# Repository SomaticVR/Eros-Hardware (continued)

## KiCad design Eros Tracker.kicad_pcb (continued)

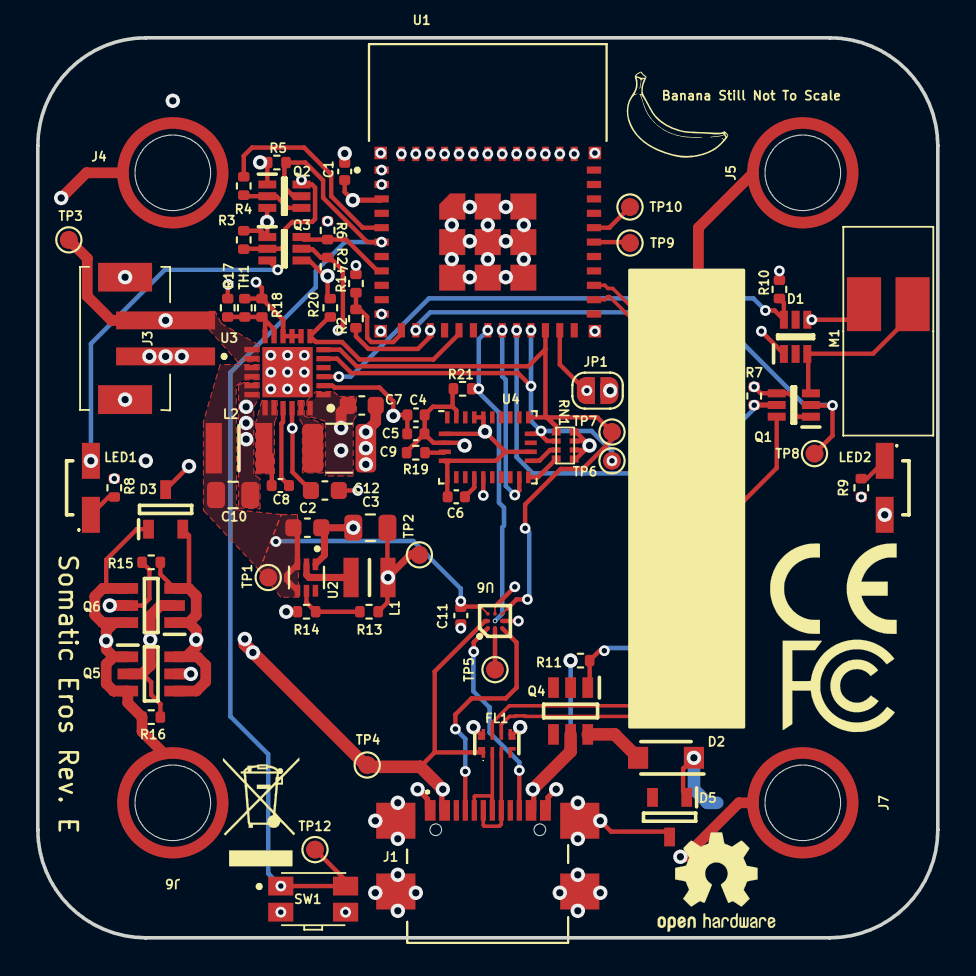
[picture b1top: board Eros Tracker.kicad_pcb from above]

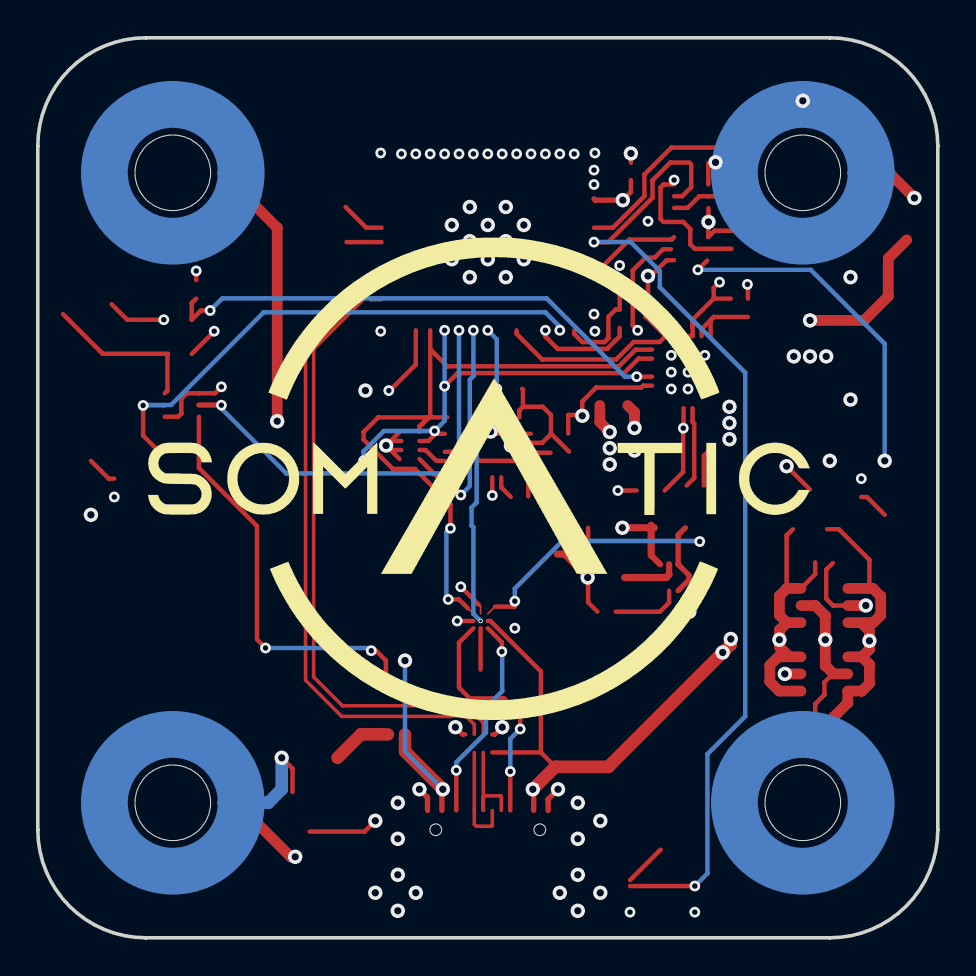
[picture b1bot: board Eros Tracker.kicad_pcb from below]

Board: 4 copper layers, 50.0 x 50.0 mm, 85 parts (5 on the bottom side), 49 nets.

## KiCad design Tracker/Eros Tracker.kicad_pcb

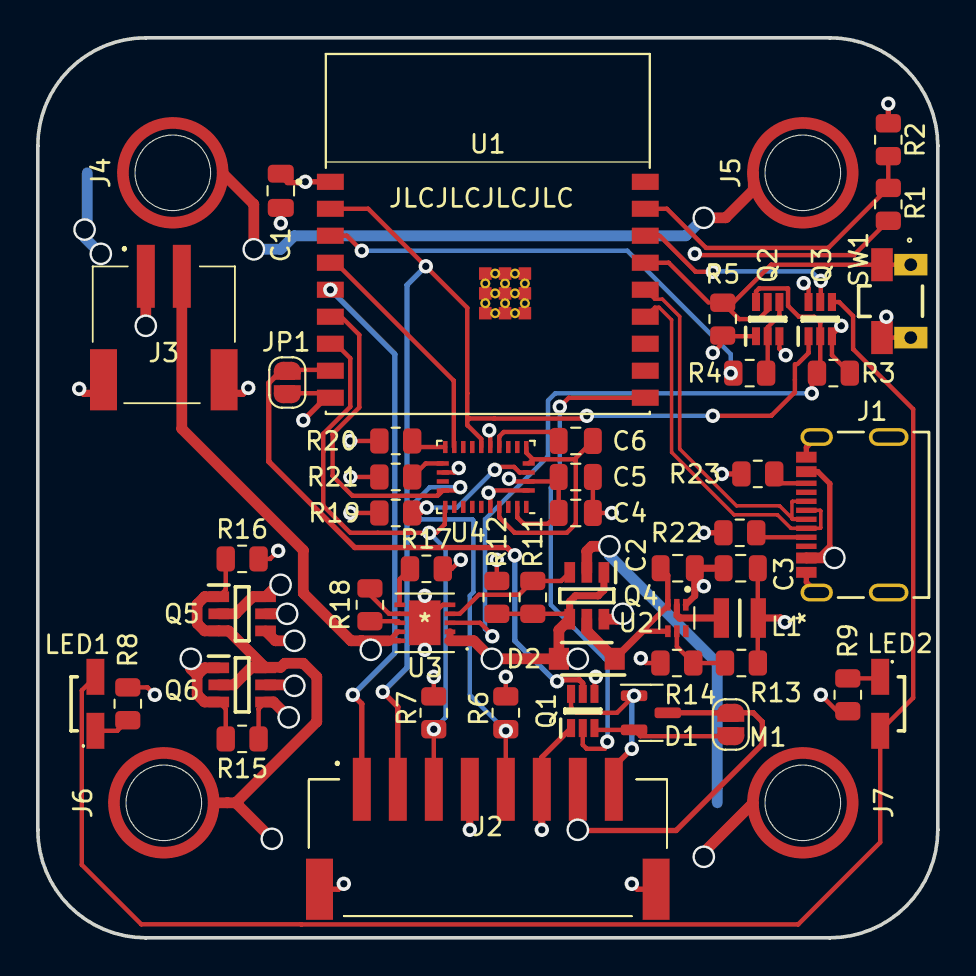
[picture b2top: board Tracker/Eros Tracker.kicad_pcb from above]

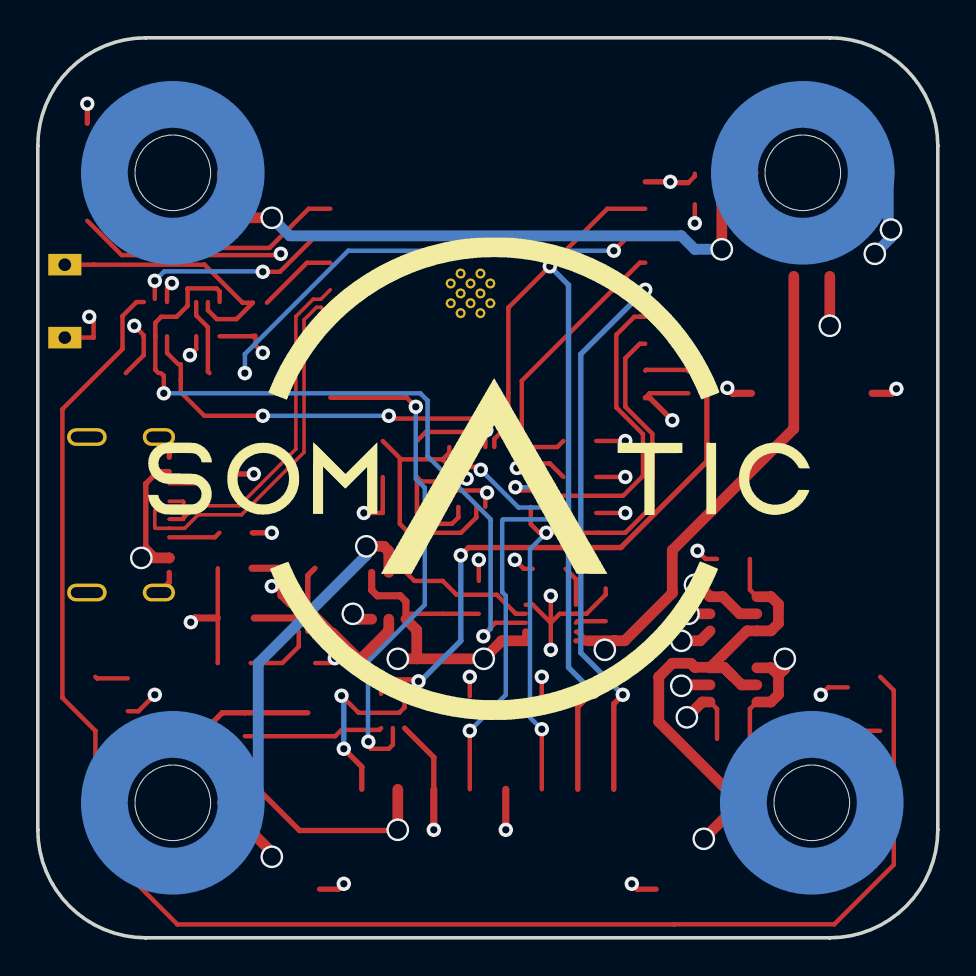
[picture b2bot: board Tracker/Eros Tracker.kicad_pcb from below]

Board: 4 copper layers, 50.0 x 50.0 mm, 57 parts (4 on the bottom side), 40 nets.

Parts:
C1, C4, C5, C6: 0.1uF; C_0805_2012Metric
C2: 4.7uF; C_0805_2012Metric
C3: 22uF; C_0805_2012Metric
D1: BAT54C; SOT-23
D2: SS34FA; SODFL3618X143N
J1: 2171790001; 2171790001_MOL
J2: S8B-PH-SM4-TB(LF)(SN); S8BPHSM4TBLFSN
J3: S2B-PH-SM4-TB(LF)(SN); S2BPHSM4TBLFSN
J4, J5, J6, J7: 24881; 2488x-NPTH
J8, J9, J10, J11: 10mmDisc
JP1: BOOT; SolderJumper-2_P1.3mm_Open_RoundedPad1.0x1.5mm
L1: 1uH; DFE2HCAH1R0MJ0L
LED1, LED2: APDA3020LVBC_D; APDA3020LVBCD
M1: Motor_DC; SolderJumper-2_P1.3mm_Open_RoundedPad1.0x1.5mm
Q1, Q2: NX138BKSX; SOT65P210X110-6N
Q3: DMP31D7LDW-7; SOT65P210X110-6N
Q4: DMP2240UDM-7; SOT95P285X140-6N
Q5, Q6: DMC1028UVT-7; SOT95P285X140-6N
R1, R13: 45k3 1%; R_0805_2012Metric
R2, R5, R11, R12, R14, R15, R16, R18, R19: 10k 1%; R_0805_2012Metric
R3, R4: 100k; R_0805_2012Metric
R6, R7, R20, R21: 2.2k; R_0805_2012Metric
R8, R9: 22R; R_0805_2012Metric
R17: 835R; R_0805_2012Metric
R22, R23: 5k1; R_0805_2012Metric
SW1: EVQ-P7A01P; EVQ-9P701P
U1: ESP32-C3-WROOM-02-N4; ESP32-C3-WROOM-02-N4-MODULE_ESP32-C3-WROOM-02-H4
U2: TPS62A01A; TPS62A0xA-SOT-563
U3: MCP73834-FCI/MF; MCP73834-FCI-MF
U4: BNO086; LGA-28_5.2x3.8mm_P0.5mm

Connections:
+3V3: C1.1, C3.1, C4.1, C5.1, J2.4, L1.2, Q2.3 (D2), Q3.3 (D2), Q3.6 (D1), R3.1, R6.1, R7.1, R13.1, R19.1, R20.1, R21.1, SW1.3 (COM_1), SW1.4 (COM_2), U1.1 (3V3), U4.3 (VDD), U4.10 (CLKSEL0), U4.28 (VDDIO)
+BATT: D1.3, J2.7, J3.2, M1.1 (+), Q4.6 (D1), R1.1, U3.9 (VBAT), U3.10 (VBAT)
/Eros Tracker BNO086 IMU/I2C_SCL: J2.5, R6.2, U1.6 (IO7), U4.19 (H_SCL/SCK/RX)
/Eros Tracker BNO086 IMU/I2C_SDA: J2.3, R7.2, U1.7 (IO8), U4.20 (H_SDA/H_CIPO/TX)
/Eros Tracker BNO086 IMU/INT: U1.4 (IO5), U4.14 (~H_INT)
/Eros Tracker BNO086 IMU/~RESET: J2.2, Q3.1 (S1), U1.2 (EN), U4.11 (~RESET)
/Eros Tracker Connectors/-EXT_MOTOR: D1.1, J2.8, Q1.6 (D1)
/Eros Tracker Connectors/INT: J2.1, U1.5 (IO6)
/Eros Tracker Connectors/POWER_VIN1: J4.1, J5.1, Q5.2 (S2), Q5.6 (D1), Q6.1 (G1), Q6.3 (G2), R15.2
/Eros Tracker Connectors/POWER_VIN2: J6.1, J7.1, Q5.1 (G1), Q5.3 (G2), Q6.2 (S2), Q6.6 (D1), R16.1
/Eros Tracker Connectors/USB_D+: J1.A6 (DP1), J1.B6 (DP2), U1.14 (IO19)
/Eros Tracker Connectors/USB_D-: J1.A7 (DN1), J1.B7 (DN2), U1.13 (IO18)
/Eros Tracker Connectors/VBUS: D2.2 (A), J1.A4/B9 (VBUS), J1.B4/A9 (VBUS), Q4.1 (G1), Q4.4 (D2), Q5.4 (D2), Q6.4 (D2), R11.1, R12.1, R15.1, U3.1 (VDD), U3.2 (VDD)
/Eros Tracker Connectors/VBUS_OUT: J8.1, Q4.2 (S2)
/Eros Tracker Microcontroller/ENABLE_LATCH: R4.1, U1.3 (IO4)
/Eros Tracker Microcontroller/TACT_MOTOR0: JP1.2 (B), Q1.5 (G2), U1.8 (IO9)
/Eros Tracker Microcontroller/TACT_MOTOR1: Q1.2 (G1), U1.10 (IO10)
/Eros Tracker Microcontroller/~BUTTON_INPUT: Q2.5 (G2), R5.1, SW1.1 (NO_1), SW1.2 (NO_2), U1.15 (IO3)
/Eros Tracker Microcontroller/~LED: Q3.5 (G2), U1.16 (IO2)
/Eros Tracker Power & Battery/VIN: C2.1, D2.1 (K), Q4.5 (S1), U2.3 (VIN), U2.4 (EN)
/Eros Tracker Power & Battery/~BAT_STAT_CHARGING: Q2.6 (D1), Q3.2 (G1), R3.2, U3.3 (STAT1)
/Eros Tracker Power & Battery/~BAT_STAT_CHRG_DONE: Q4.3 (G2), R11.2, U3.4 (STAT2)
GND: C1.2, C2.2, C3.2, C4.2, C5.2, J1.13 (Shield), J1.14 (Shield), J1.15 (Shield), J1.16 (Shield), J1.A1/B12 (GND), J1.B1/A12 (GND), J2.6, J2.MP1, J2.MP2, J3.1, J3.MP1, J3.MP2, J11.1, JP1.1 (A), Q1.1 (S1), Q1.4 (S2), Q2.1 (S1), Q5.5 (S1), Q6.5 (S1), R2.2, R5.2, R8.2, R9.2, R12.2, R14.2, R16.2, R17.2, R18.2, R22.2, R23.2, U1.9 (GND), U1.19 (GND), U1.20 (GND), U1.21 (GND), U1.22 (GND), U1.23 (GND), U1.24 (GND), U1.25 (GND), U1.26 (GND), U1.27 (GND), U1.28 (GND), U1.29 (GND), U1.30 (GND), U1.31 (GND), U1.32 (GND), U1.33 (GND), U1.34 (GND), U1.35 (GND), U1.36 (GND), U1.37 (GND), U1.38 (GND), U1.39 (GND), U2.1 (GND), U3.5 (VSS), U3.7 (*TE), U3.11 (EP), U4.2 (GND), U4.17 (SA0/H_COPI), U4.25 (GNDIO)
unnamed: J1.A5 (CC1), R22.1
unnamed: J1.B5 (CC2), R23.1
unnamed: LED1.2 (A), LED2.2 (A), Q3.4 (S2)
unnamed: LED1.1 (K), R8.1
unnamed: LED2.1 (K), R9.1
unnamed: D1.2, M1.2 (-), Q1.3 (D2)
unnamed: Q2.2 (G1), Q2.4 (S2), R4.2
unnamed: R1.2, R2.1, U1.17 (IO1)
unnamed: R13.2, R14.1, U2.5 (FB)
unnamed: L1.1, U2.2 (SW)
unnamed: R17.1, U3.6 (PROG)
unnamed: R18.1, U3.8 (THERM)
unnamed: C6.1, U4.9 (CAP)
unnamed: R20.2, U4.15 (ENV_SCL)
unnamed: R21.2, U4.16 (ENV_SDA)
unnamed: C6.2, U4.5 (PS1), U4.6 (PS0/WAKE), U4.26 (XOUT32)
unnamed: R19.2, U4.4 (~BOOTN)

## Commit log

2023-06-04 Midway through board layout
2023-06-08 Alpha release
2023-07-19 Added cuts and jumps for Rev A
2023-08-15 Added basic testing software
2023-10-31 Rev B release + Panel. pcb and sch changes lost. panel shows updates.
2023-10-31 RevC release. Power passthrough, battery voltage monitoring, IMU interrupt line fixed. TVS diodes added to all human-reachable connections.
2023-10-31 Folder reorginization and .gitignore update
2024-04-02 Rev D realease
2025-02-08 Rev E release
